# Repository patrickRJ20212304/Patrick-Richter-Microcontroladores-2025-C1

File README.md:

# Patrick-Richter-Microcontroladores-2025-C1

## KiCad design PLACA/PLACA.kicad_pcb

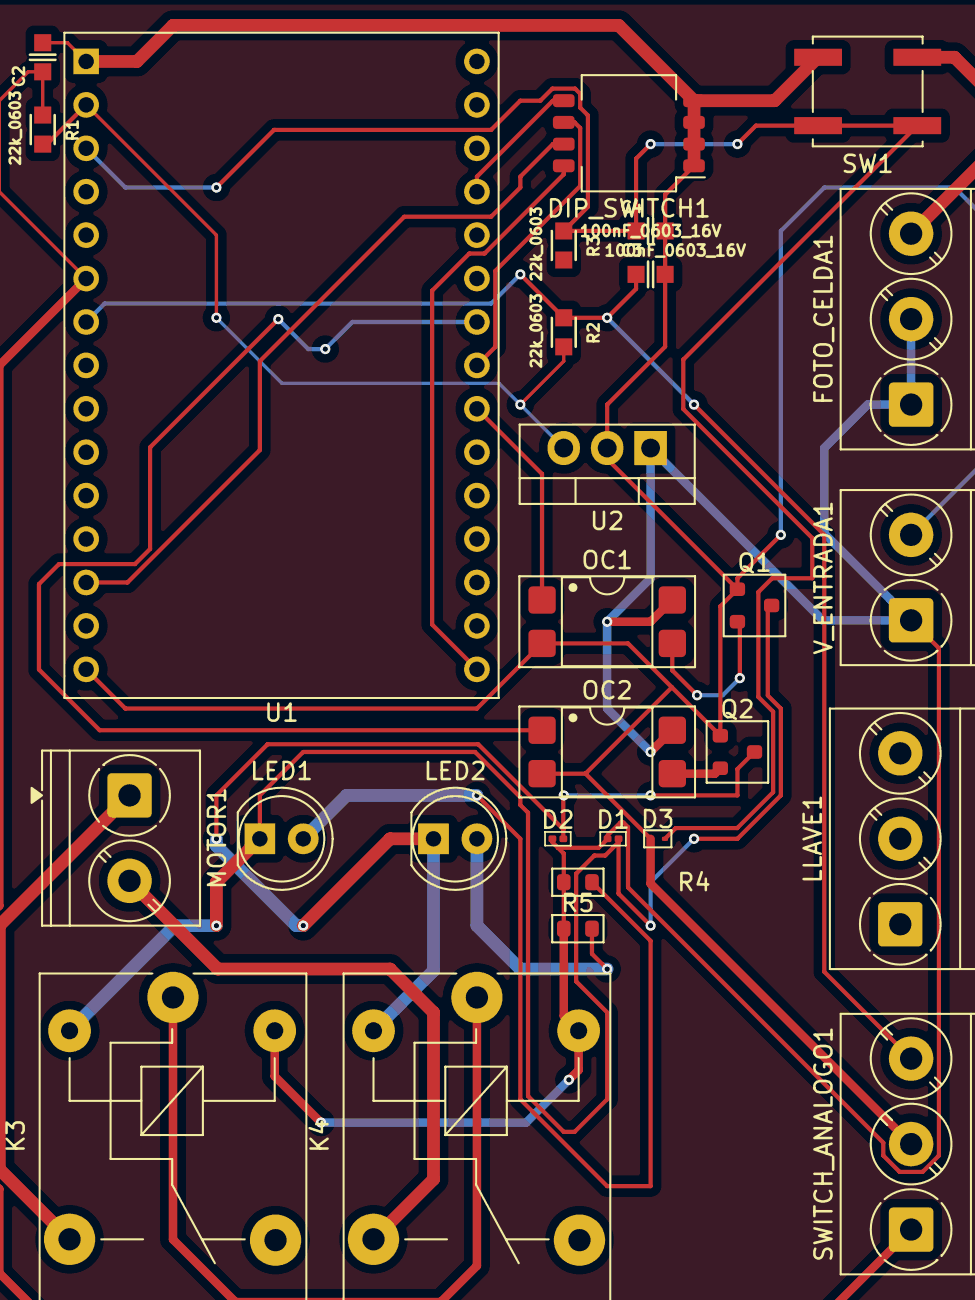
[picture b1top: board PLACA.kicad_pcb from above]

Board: 2 copper layers, 28 parts (0 on the bottom side), 21 nets.

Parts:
C2, C3, C4: 100nF_0603_16V; C_0603
D1, D2: 1N914BWS; D_0201_0603Metric_TVS
D3: ESD9B3.3; D_SOD-923_TVS
DIP_SWITCH1: SW_DIP_x04; SW_DIP_SPSTx04_Slide_KingTek_DSHP04TS_W7.62mm_P1.27mm
FOTO_CELDA1: Screw_Terminal_01x03; TerminalBlock_Phoenix_PT-1,5-3-5.0-H_1x03_P5.00mm_Horizontal
K3, K4: SANYOU_SRD_Form_C; Relay_SPDT_SANYOU_SRD_Series_Form_C
LED1, LED2: LED_0603_Red; LED_D5.0mm
LLAVE1: Screw_Terminal_01x03; TerminalBlock_Phoenix_PT-1,5-3-5.0-H_1x03_P5.00mm_Horizontal
MOTOR1: -; TerminalBlock_Phoenix_PT-1,5-2-5.0-H_1x02_P5.00mm_Horizontal
OC1, OC2: PC817; DIP-4_W7.62mm_SMDSocket_SmallPads
Q1, Q2: 2N2219; SOT-23
R1, R2, R3: 22k_0603; R_0603
R4, R5: 2k; R_0603_1608Metric
SW1: SW_Push; SW_Push_1P1T_NO_CK_KSC7xxJ
SWITCH_ANALOGO1: Screw_Terminal_01x03; TerminalBlock_Phoenix_PT-1,5-3-5.0-H_1x03_P5.00mm_Horizontal
U1: ESP32-WROOM-32D; ESP32-C3-DevKitM-1
U2: LM7805CT; TO-220-3_Vertical
V_ENTRADA1: 12V; TerminalBlock_Phoenix_PT-1,5-2-5.0-H_1x02_P5.00mm_Horizontal

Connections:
/BOARD/12V: D1.1 (K), D2.1 (K), FOTO_CELDA1.1, FOTO_CELDA1.2, K3.5, K4.5, OC1.4, OC2.4, R4.1, R5.1, U2.1 (IN), V_ENTRADA1.1
/BOARD/LS/5V: R1.1, R2.1, U1.2 (VDD), U2.3 (OUT)
/BOARD/LSA: C3.1, R2.2, SWITCH_ANALOGO1.3, U1.7 (IO35)
/BOARD/LSC: C2.1, R1.2, SWITCH_ANALOGO1.1, U1.6 (IO34)
/BOARD/MICRO/MOTOR_DERECHA: OC1.1, U1.22 (SDI/SD1)
/BOARD/MICRO/MOTOR_IZQUIERDA: OC2.1, U1.24 (IO2)
/BOARD/MICRO/RESET: C4.1, D3.2 (A), R3.2, SW1.2, U1.3 (EN)
/BOARD/MOTOR_DERECHA: K3.3, MOTOR1.1
/BOARD/MOTOR_IZQUIERDA: K4.3, MOTOR1.2
/BOARD/SW1: DIP_SWITCH1.8, U1.16 (IO13)
/BOARD/SW2: DIP_SWITCH1.7, U1.13 (IO14)
/BOARD/SW3: DIP_SWITCH1.6, U1.23 (IO15)
/BOARD/SW4: DIP_SWITCH1.5, U1.27 (IO16)
GND: C2.2, C3.2, C4.2, D3.1 (K), DIP_SWITCH1.1, DIP_SWITCH1.2, DIP_SWITCH1.3, DIP_SWITCH1.4, FOTO_CELDA1.3, OC1.2, OC2.2, Q1.1 (E), Q2.1 (E), SW1.1, SWITCH_ANALOGO1.2, U1.1 (GND), U1.15 (GND), U2.2, V_ENTRADA1.2
LINE: K3.1, K4.1
unnamed: D1.2 (A), K3.2, LED1.1 (K), Q1.3 (C)
unnamed: D2.2 (A), K4.2, LED2.1 (K), Q2.3 (C)
unnamed: LED1.2 (A), R4.2
unnamed: LED2.2 (A), R5.2
unnamed: OC1.3, Q1.2 (B)
unnamed: OC2.3, Q2.2 (B)

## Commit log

2025-04-24 Create build
